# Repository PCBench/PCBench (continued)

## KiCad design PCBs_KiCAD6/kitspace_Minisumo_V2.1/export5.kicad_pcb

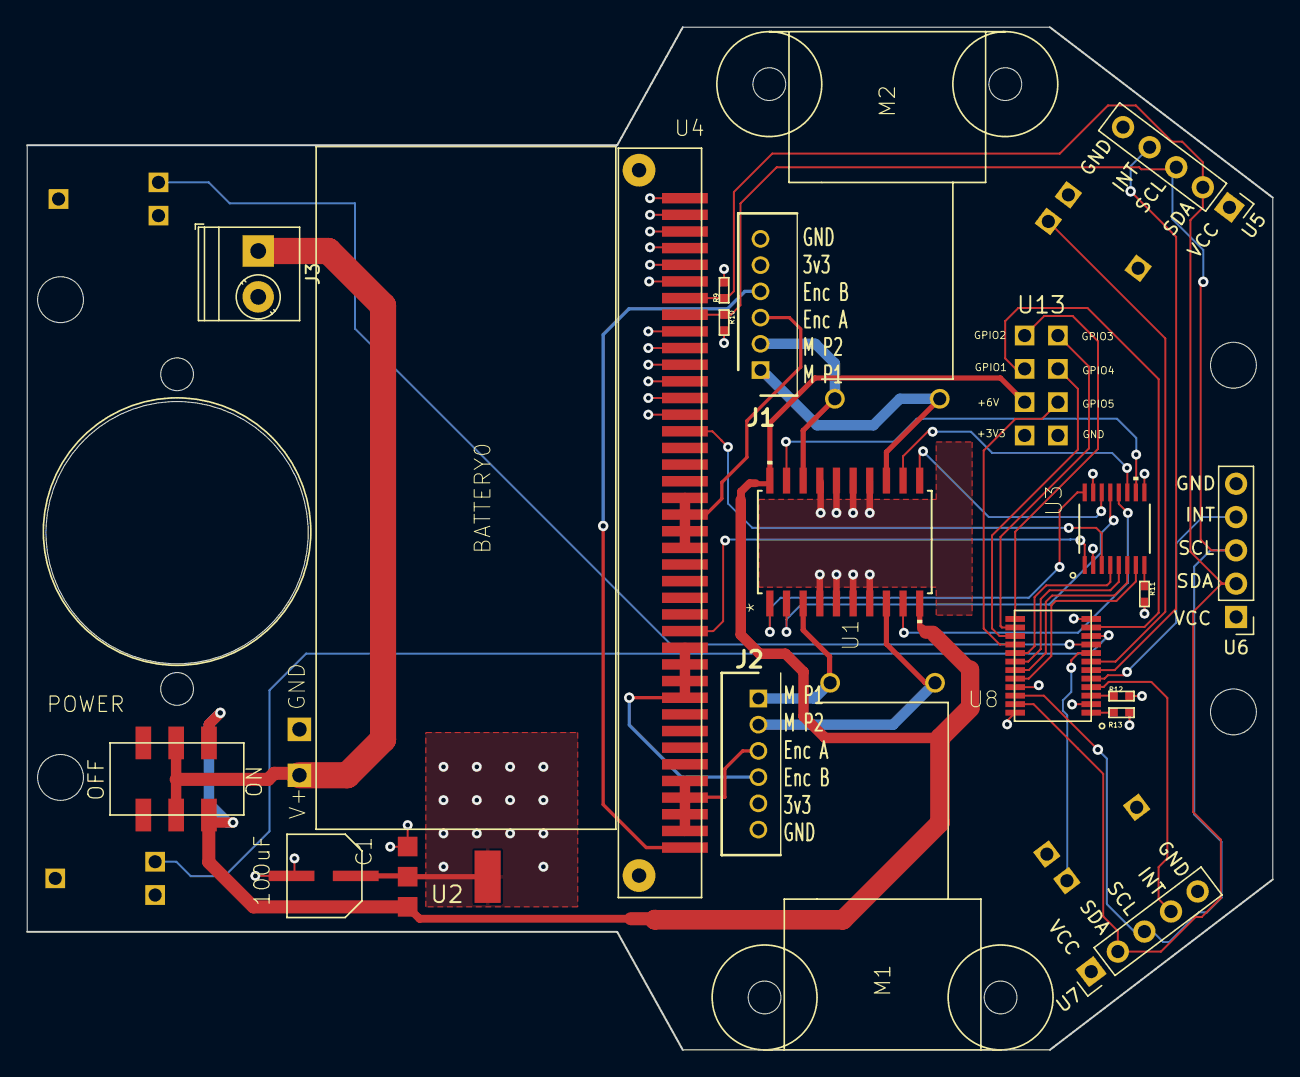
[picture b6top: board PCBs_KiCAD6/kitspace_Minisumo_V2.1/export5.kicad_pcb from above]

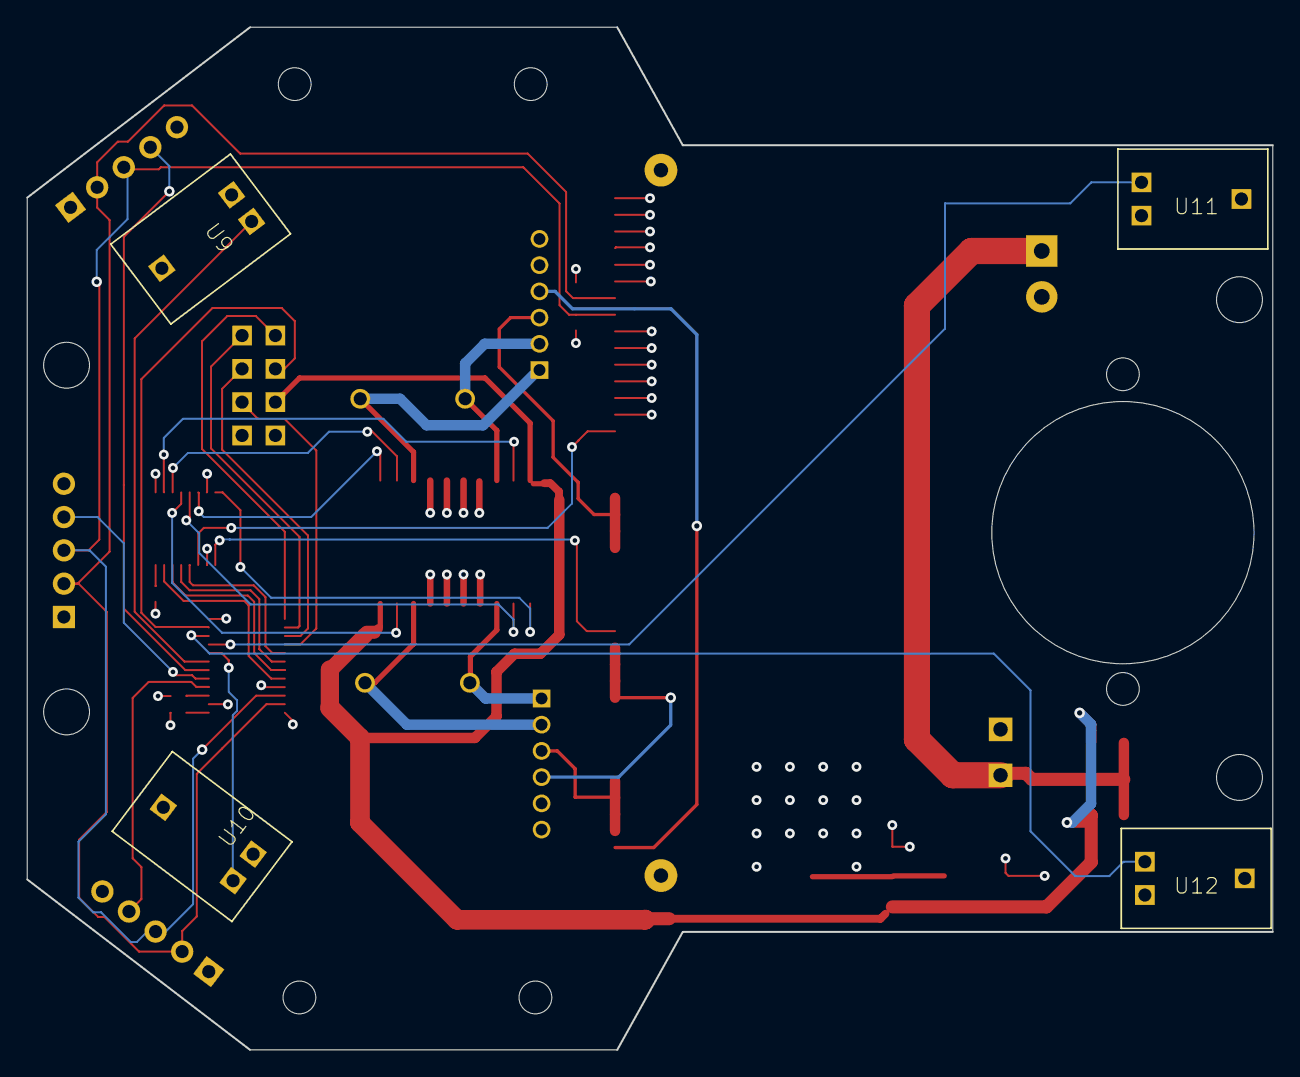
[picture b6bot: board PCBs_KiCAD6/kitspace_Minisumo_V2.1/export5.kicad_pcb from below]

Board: 2 copper layers, 95.0 x 78.0 mm, 31 parts (4 on the bottom side), 41 nets.

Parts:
@HOLE0, @HOLE1, @HOLE2, @HOLE3: (no value)
BATTERY0: BATTERY_HOLDER_AAA_2X2
C1: 100uF; ALUMINUM_WURTH_100UF_865080243007
J1: Right Motor; SHDR6W50P0X200_1X6_1390X450X600P
J2: Left Motor; SHDR6W50P0X200_1X6_1390X450X600P
J3: Screw_Terminal_01x02; TerminalBlock_Phoenix_PT-1,5-2-3.5-H_1x02_P3.50mm_Horizontal
M1, M2: N20_MOTOR; N20-MOTOR-BRACKET
R9, R10, R11, R12, R13: 10k; RES_0402
S1: POWER; SWITCH_JS202011SCQN
U1: L293DD; SO-20
U2: LM1117; SOT-223
U3: TXB0106PWRPW16-L; PW16-L
U4: BBC Micro:bit; CYCLONE_MICROBIT_VERTICAL
U5: VL53L1X Right; PinHeader_1x05_P2.54mm_Vertical
U6: VL53L1X Center; PinHeader_1x05_P2.54mm_Vertical
U7: VL53L1X Left; PinHeader_1x05_P2.54mm_Vertical
U8: TCA9539PWR; 24-TSSOP
U9: NW; QRE1113_MODULE
U10: NE; QRE1113_MODULE
U11: SW; QRE1113_MODULE
U12: SE; QRE1113_MODULE
U13: SUMO_IO
U$1: CASTER

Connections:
+3V3: C1.+, J1.5, J2.5, R9.P$2, R10.P$2, R11.P$2, R12.P$2, R13.P$2, U2.P$2, U2.VOUT$1, U3.2, U4.3.3V@9, U4.3.3V@10, U4.3.3V@11, U4.3.3V@12, U4.3.3V@13, U4.3.3V@14, U5.1, U6.1, U7.1, U8.24, U9.+3V3, U10.+3V3, U11.+3V3, U12.+3V3, U13.3V3
+5V: S1.3, S1.6, U1.10, U1.20, U2.VIN, U3.15, U13.6V
/INPUT_1: U3.4, U8.17
/INPUT_2: U3.5, U8.18
/INPUT_3: U3.6, U8.19
/INPUT_4: U3.7, U8.20
/IO1: U8.11, U13.GPIO1
/IO2: U8.13, U13.GPIO2
/IO3: U8.14, U13.GPIO3
/IO4: U8.15, U13.GPIO4
/IO5: U8.16, U13.GPIO5
/ML1: J2.1, M1.1, U1.3
/ML2: J2.2, M1.2, U1.8
/ML_A: J2.3, U4.P0_ANALOG_IN@36, U4.P0_ANALOG_IN@37, U4.P0_ANALOG_IN@38, U4.P0_ANALOG_IN@39
/ML_B: J2.4, U4.P1_ANALOG_IN@28, U4.P1_ANALOG_IN@29, U4.P1_ANALOG_IN@30, U4.P1_ANALOG_IN@31
/MR1: J1.1, M2.1, U1.13
/MR2: J1.2, M2.2, U1.18
/MR_A: J1.3, U4.P2_ANALOG_IN@19, U4.P2_ANALOG_IN@20, U4.P2_ANALOG_IN@21, U4.P2_ANALOG_IN@22
/MR_B: J1.4, U4.P3_LED_COL_1_ANALOG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
/NE: U8.8, U10.SIGNAL
/NW: U8.7, U9.SIGNAL
/SCL: R10.P$1, U4.P21_SCL, U5.3, U6.3, U7.3, U8.22
/SDA: R9.P$1, U4.P20_SDA, U5.2, U6.2, U7.2, U8.23
/SE: U8.10, U12.SIGNAL
/SW: U8.9, U11.SIGNAL
/XS1: U7.4, U8.4
/XS2: U6.4, U8.5
/XS3: U5.4, U8.6
GND: BATTERY0.-, C1.-, J1.6, J2.6, J3.2, U1.4, U1.5, U1.6, U1.7, U1.14, U1.15, U1.16, U1.17, U2.GND, U3.9, U4.GND@1, U4.GND@2, U4.GND@3, U4.GND@4, U4.GND@5, U4.GND@6, U5.5, U6.5, U7.5, U8.2, U8.12, U8.21, U9.GND, U10.GND, U11.GND, U12.GND, U13.GND
unnamed: BATTERY0.+, J3.1, S1.2, S1.5
unnamed: R11.P$1, U3.8
unnamed: R12.P$1, U8.3
unnamed: R13.P$1, U8.1
unnamed: U1.1, U3.16
unnamed: U1.2, U3.13
unnamed: U1.9, U3.12
unnamed: U1.11, U3.14
unnamed: U1.12, U3.11
unnamed: U1.19, U3.10
unnamed: U3.1, U4.P8
unnamed: U3.3, U4.P16

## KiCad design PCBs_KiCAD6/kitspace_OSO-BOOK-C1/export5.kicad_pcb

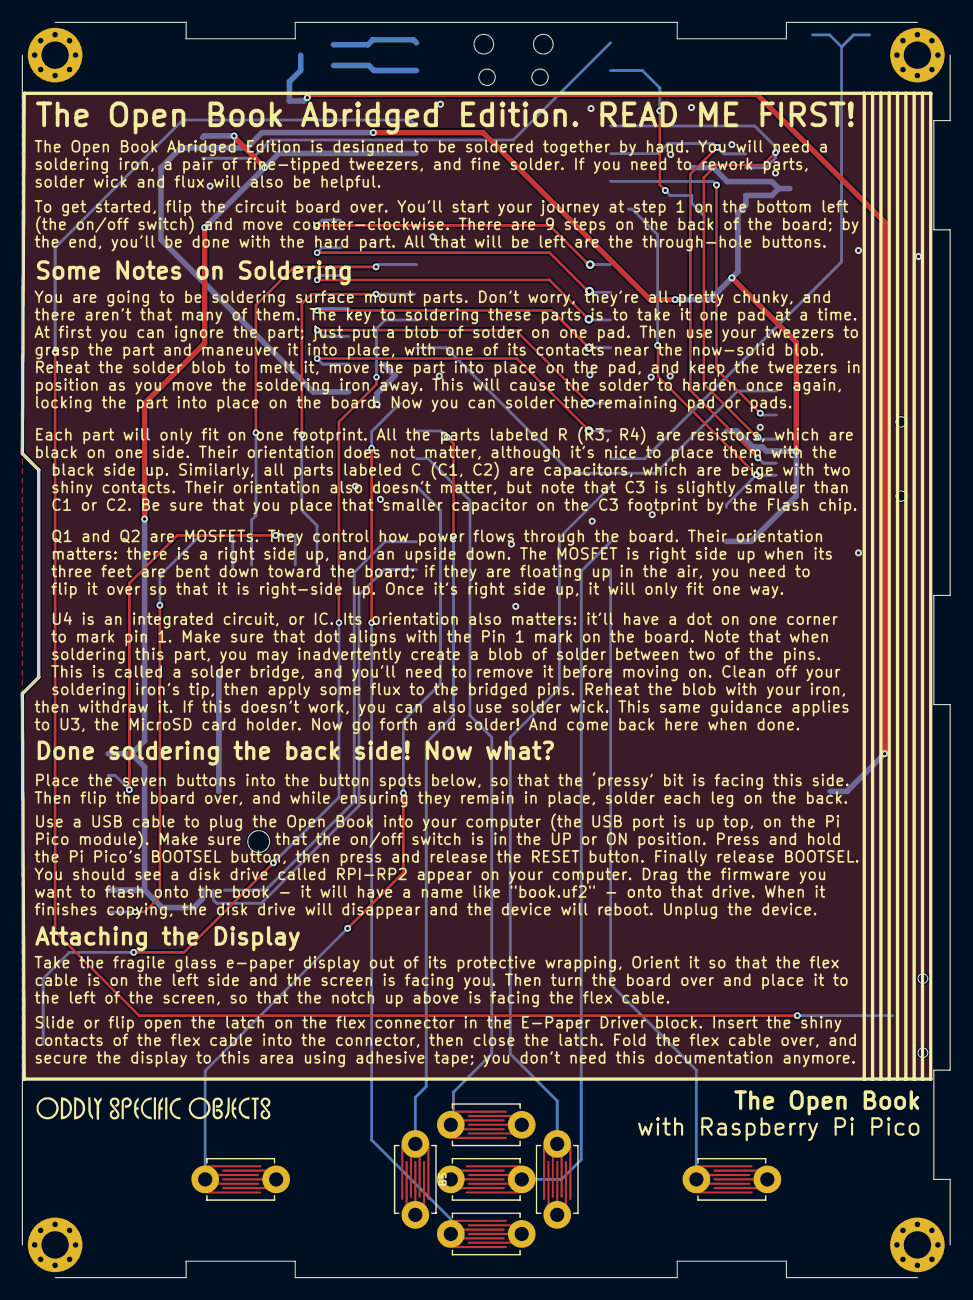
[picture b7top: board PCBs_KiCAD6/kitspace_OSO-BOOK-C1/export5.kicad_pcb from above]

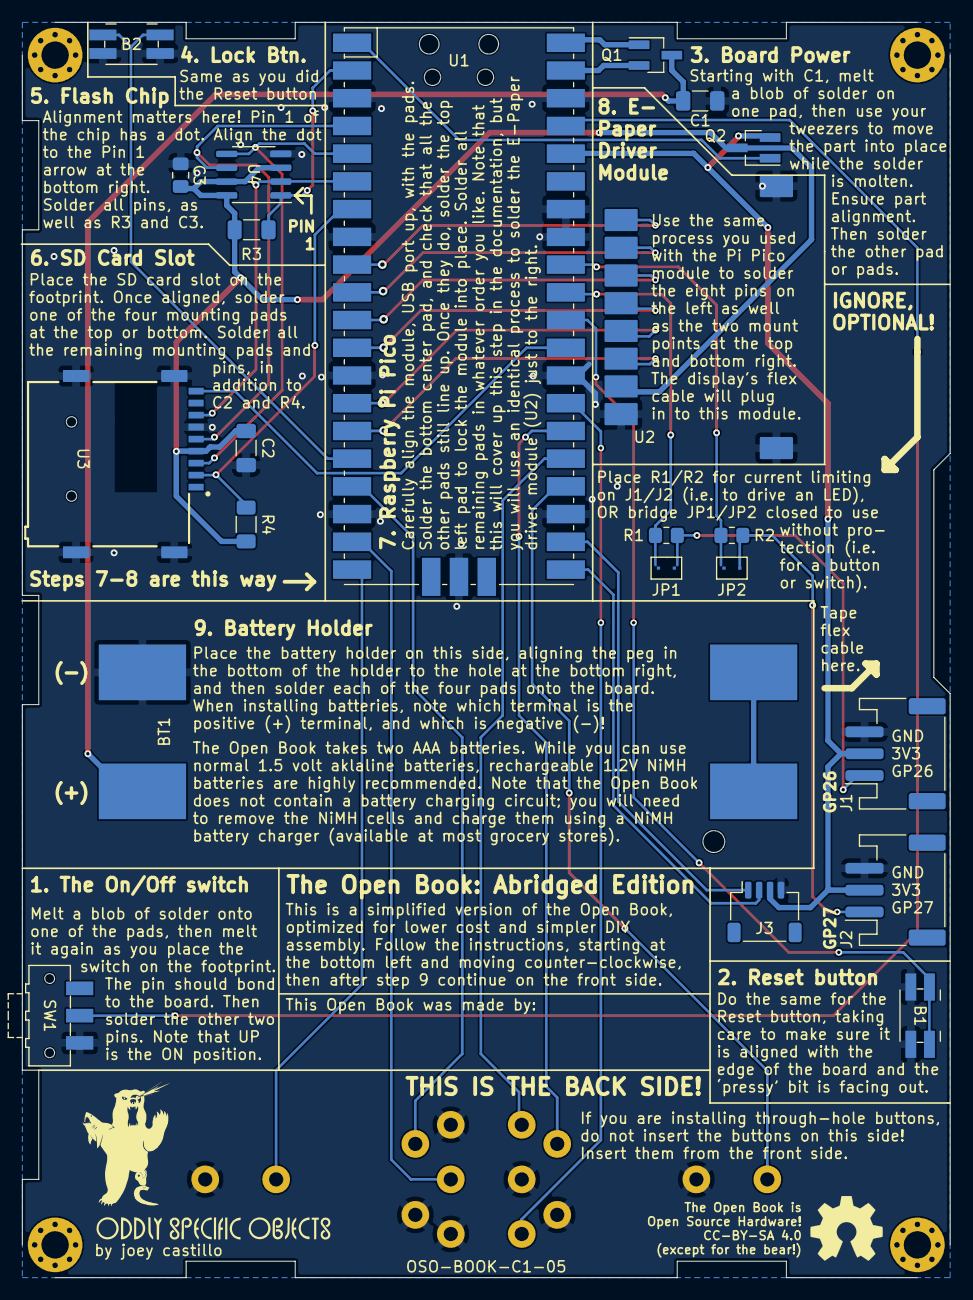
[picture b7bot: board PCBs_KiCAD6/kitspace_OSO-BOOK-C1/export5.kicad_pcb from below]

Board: 2 copper layers, 85.0 x 115.0 mm, 29 parts (22 on the bottom side), 35 nets.

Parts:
B1, B2: SW_Push; Panasonic_EVQPUJ_EVQPUA
B3, B4, B5, B6, B7, B8, B9: SW_Push; TACT_PANA-EVQ-BUTTONPAD
BT1: Battery; AAA_SMT
C1, C2: 10µF; C_1206_3216Metric_Pad1.33x1.80mm_HandSolder
C3: 1µF; C_0805_2012Metric_Pad1.18x1.45mm_HandSolder
J1, J2: JST-PH3; JST_PH_S3B-PH-SM4-TB_1x03-1MP_P2.00mm_Horizontal
J3: JST-PH4; JST_SH_SM04B-SRSS-TB_1x04-1MP_P1.00mm_Horizontal
JP1, JP2: Jumper_2_Open; SolderJumper-2_P1.3mm_Open_TrianglePad1.0x1.5mm
Q1, Q2: Q_PMOS_GSD; SOT-23_Handsoldering
R1, R2: 1k; R_0805_2012Metric_Pad1.20x1.40mm_HandSolder
R3, R4: 10K; R_1206_3216Metric_Pad1.30x1.75mm_HandSolder
SW1: SW_SPDT; SW_SPDT_CK-JS102011SAQN
U1: Pico; RPi_Pico_SMD
U2: OSO-BOOK-C2-01
U3: MEM2075; GCT_MEM2075-00-140-01-A
U4: GD25Q16C; SOIC-8_3.9x4.9mm_P1.27mm

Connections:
+3.3VP: C2.2, C3.1, Q2.3, R3.2, R4.2, U2.7, U3.P4, U4.3, U4.7, U4.8
+3V3: J1.2, J2.2, J3.3, Q2.2, U1.36
+BATT: BT1.1, C1.1, Q1.3
/BABEL_CS: R3.1, U1.2, U4.1
/BTN_DOWN: B8.1, U1.27
/BTN_LEFT: B5.1, U1.26
/BTN_LOCK: B2.1, U1.16
/BTN_NEXT: B4.1, U1.20
/BTN_PREV: B3.1, U1.24
/BTN_RIGHT: B9.1, U1.17
/BTN_SEL: B7.1, U1.19
/BTN_UP: B6.1, U1.25
/DISPLAY_BUSY: U1.9, U2.1
/DISPLAY_CS: U1.12, U2.4
/DISPLAY_DC: U1.11, U2.3
/DISPLAY_MOSI: U1.15, U2.6
/DISPLAY_RESET: U1.10, U2.2
/DISPLAY_SCK: U1.14, U2.5
/EN: SW1.2, U1.37
/GP26: JP1.2, R1.1, U1.31
/GP27: JP2.2, R2.1, U1.32
/MISO: U1.6, U3.P7, U4.2
/MOSI: U1.5, U3.P3, U4.5
/RESET: B1.1, U1.30
/RX/SCL: J3.1, U1.22
/SCK: U1.4, U3.P5, U4.6
/SD_CD: U1.29, U3.P9
/SD_CS: R4.1, U1.7, U3.P2
/TX/SDA: J3.2, U1.21
/_GP26: J1.1, JP1.1, R1.2
/_GP27: J2.1, JP2.1, R2.2
/~EN2: Q2.1, U1.1
GND: B1.2, B2.2, B3.2, B4.2, B5.2, B6.2, B7.2, B8.2, B9.2, BT1.2, C1.2, C2.1, C3.2, J1.3, J2.3, J3.4, SW1.3, U1.3, U1.8, U1.13, U1.18, U1.23, U1.28, U1.33, U1.34, U1.38, U1.42, U2.8, U2.9, U2.10, U3.P6, U3.SH1, U3.SH2, U3.SH3, U3.SH4, U4.4
VBUS: Q1.1, U1.40
VCC: Q1.2, U1.39

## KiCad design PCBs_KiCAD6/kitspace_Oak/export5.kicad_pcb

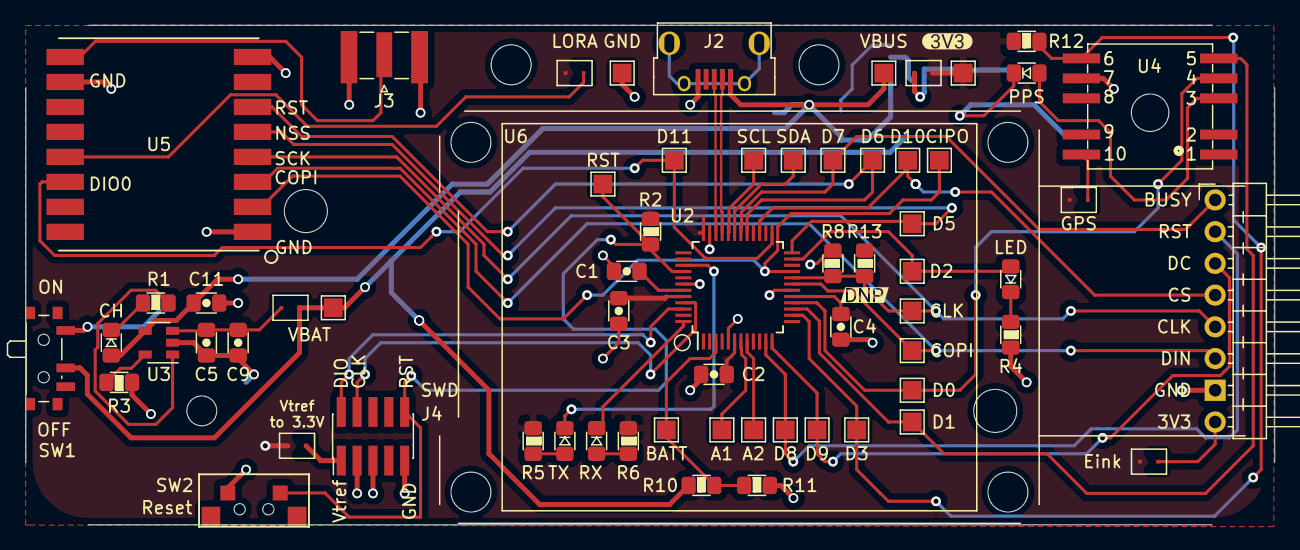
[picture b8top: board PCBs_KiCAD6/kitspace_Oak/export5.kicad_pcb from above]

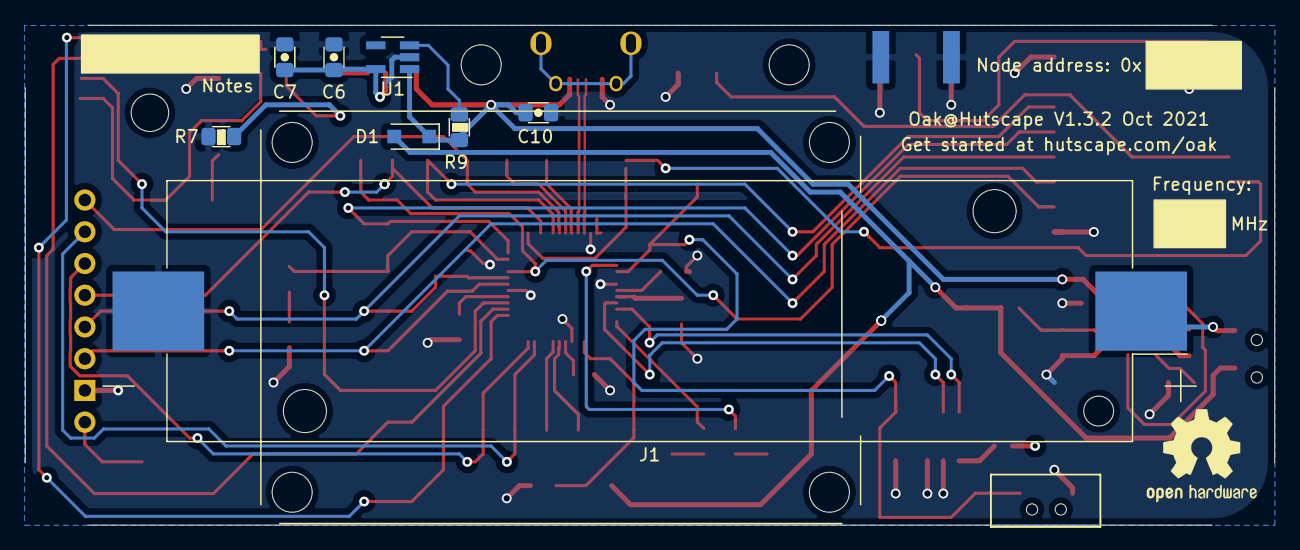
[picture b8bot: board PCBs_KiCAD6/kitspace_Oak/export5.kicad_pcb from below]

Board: 2 copper layers, 100.0 x 40.0 mm, 73 parts (8 on the bottom side), 48 nets.

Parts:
C1, C7, C9: 1uF; C_0805_2012Metric_Pad1.15x1.40mm_HandSolder
C2, C3, C4: 100nF; C_0805_2012Metric_Pad1.15x1.40mm_HandSolder
C5, C6, C10, C11: 10uF; C_0805_2012Metric_Pad1.15x1.40mm_HandSolder
D1: D_Schottky; D_SOD-123F
D2: ORANGE; LED_0805_2012Metric_Pad1.15x1.40mm_HandSolder
D3: RED; LED_0805_2012Metric_Pad1.15x1.40mm_HandSolder
D4, D5, D6: YELLOW; LED_0805_2012Metric_Pad1.15x1.40mm_HandSolder
J1: 18650 Battery holder; BatteryHolder_Keystone_1042_1x18650
J2: USB_B_Micro; USB_Micro-B_Horizontal-U254-051T-4BH23-S2B
J3: Conn_Coaxial; SMA_Samtec_SMA-J-P-X-ST-EM1_EdgeMount
J4: Conn_ARM_JTAG_SWD_10; PinHeader_2x05_P1.27mm_Vertical_SMD
JP1, JP2, JP3, JP4, JP5, JP6: SolderJumper_2_Open; SolderJumper-2_P1.3mm_Open_TrianglePad1.0x1.5mm
R1, R4, R5, R6, R7, R8: 1k; R_0805_2012Metric_Pad1.15x1.40mm_HandSolder
R2, R3, R12: 10k; R_0805_2012Metric_Pad1.15x1.40mm_HandSolder
R9, R10, R11: 100k; R_0805_2012Metric_Pad1.15x1.40mm_HandSolder
R13: DNP; R_0805_2012Metric_Pad1.15x1.40mm_HandSolder
SW1: SW_SPDT; SW_SPDT_PCM12
SW2: SW_Push; Tactile_pushbutton
TP1, TP2, TP3, TP4, TP5, TP6, TP7, TP8, TP9, TP10, TP11, TP12, TP13, TP14, TP15, TP16, TP17, TP18, TP19, TP20, TP21, TP22, TP23, TP24: TestPoint_Probe; TestPoint_Pad_1.5x1.5mm
U1: AP2112; SOT-23-5_HandSoldering
U2: ATSAMD21; TQFP-48_7x7mm_P0.5mm
U3: MCP7383; SOT-23-5
U4: PA1010D; CDTop_MT3333_PA1010D
U5: RFM95; HopeRF_RFM9X-SMD
U6: Waveshare_1in54_epaper; Waveshare_1.54_E-Ink
e: G***; label
svg2mod: G***; label

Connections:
+3V3: C2.1, C3.1, C4.1, JP1.1, JP3.1, JP4.1, JP5.1, JP6.1, R2.1, R5.1, R6.1, R12.1, R13.1, TP4.1, U2.6, U2.17, U2.36, U2.44
/A1: TP7.1, U2.7
/A2: TP6.1, U2.8
/BATT: R10.2, R11.1, TP8.1, U2.3
/CIPO: TP21.1, U2.21, U5.2
/CLK: R8.1, R13.2, TP16.1, U2.20, U5.4, U6.5
/COPI: TP5.1, U2.19, U5.3, U6.6
/EINK_BUSY: TP19.1, U2.30, U6.1
/EINK_CS: TP22.1, U2.27, U6.4
/EINK_DC: TP10.1, U2.12, U6.3
/EINK_RST: TP9.1, U2.11, U6.2
/GPS_RST: R12.2, TP11.1, U2.14, U4.6
/GPS_RX: TP12.1, U2.15, U4.5
/GPS_TX: TP13.1, U2.16, U4.4
/LED: D6.2, TP14.1, U2.23
/LORA_CS: TP15.1, U2.24, U5.5
/LORA_DATA: TP24.1, U2.25, U5.14
/LORA_RST: TP20.1, U2.29, U5.6
/RST: J4.10, R2.2, SW2.1, TP23.1, U2.40
/RX_LED: D5.1, U2.48
/SCL: TP18.1, U2.32
/SDA: TP17.1, U2.31
/SWCLK: J4.4, U2.45
/SWDIO: J4.2, U2.46
/TX_LED: D4.1, U2.39
/USB_D+: J2.3, U2.34
/USB_D-: J2.2, U2.33
/VBAT: D1.2, JP2.1, R10.1, SW1.2, TP1.1
/VBUS: C10.1, C11.2, D1.1, D2.2, J2.1, R9.2, TP2.1, U1.1, U3.4
GND: C1.1, C2.2, C3.2, C4.2, C5.1, C6.2, C7.2, C9.1, C10.2, C11.1, J1.2, J2.5, J3.2, J4.3, J4.5, J4.9, R3.1, R4.2, R7.2, R8.2, R11.2, SW2.2, TP3.1, U1.2, U2.5, U2.18, U2.35, U2.42, U3.2, U4.7, U5.1, U5.8, U5.10, U6.7
unnamed: C1.2, U2.43
unnamed: C5.2, C9.2, JP2.2, U3.3
unnamed: C6.1, C7.1, JP1.2, U1.5
unnamed: D2.1, R1.1
unnamed: D3.1, R7.1
unnamed: D3.2, U4.3
unnamed: D4.2, R5.2
unnamed: D5.2, R6.2
unnamed: D6.1, R4.1
unnamed: J1.1, SW1.1
unnamed: J3.1, U5.9
unnamed: J4.1, JP6.2
unnamed: JP3.2, U4.10
unnamed: JP4.2, U5.13
unnamed: JP5.2, U6.8
unnamed: R1.2, U3.1
unnamed: R3.2, U3.5
unnamed: R9.1, U1.3
